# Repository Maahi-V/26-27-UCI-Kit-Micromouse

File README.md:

# UCI Kit Mouse (2026-2027 Ver.)

This repository contains:
 - A template kit mouse project with KiCad
 - Short installation guide for the overall project
 - Helpful Git Commands

> [!IMPORTANT]
> Contents here are summarized from [IEEE@UCI Micromouse Website](https://ieee.ics.uci.edu/micromouse/mm_index.html).
> More details of the tools installed will be under "Modules" and "Lectures."

## Prerequistes

### KiCad
> [!NOTE]
> All teamates should install the same version of KiCad, preferably the newest
> stable release here: https://www.kicad.org/download/. 
> Files modified from newer versions can no longer be read by older versions.

*The installation guide will be using KiCad ver. 10.5*

<details>
<summary><b>Windows</b></summary>

1. Download and Launch the installer: https://www.kicad.org/download/windows/

2. Select **Next** 2 times, and give permissions to the installer.

3. At "Choose Components," make sure all check boxes are selected 
(should be default)

4. Select **Next**, and then install.
</details>

<details>
<summary><b>macOS</b></summary>

1. Download the installer: https://www.kicad.org/download/macos/

2. Double-click `kicad-unified-universal-#.#.#.dmg` file in finder

3. Click and drag the `KiCad.app` to Application folder.

4. Close the window, and Eject the `.dmg` file from Finder.

</details>

<details>
<summary><b>Linux</b></summary>
Install as an AppImage or use your desired package manager. <br></br>

> [!NOTE]
> KiCad does not support Wayland,
> but the AppImage version defaults to Wayland instead of 
> Xwayland under GTK3. Installing via PPAs instead defaults to Xwayland, 
> likely bringing graphical bugs.

</details>

---
### Git
Check if Git is installed with this command:
```sh
git --version
```

If git is missing, here are official steps in 
[installing Git](https://git-scm.com/install/), and
a recommended step-by-step installation will be provided below.

<details>
<summary><b>Windows</b></summary>

1. Install **Git for Windows** from this link: [https://git-scm.com/install/windows](https://git-scm.com/install/windows).

2. After installing the executable, give the installer permissions.

3. Select **Next** 4 times, and reach "Choosing the default editor used by Git"

Choose your favorite editor, and after setup you can still change the 
default editor with this command:
```sh
git config --global core.editor "editor-name"
```

4. Select **Next** to "Adjusting the name of the initial branch in 
new repositories"
- Use default branch name as `main`, since GitHub defaults to `main` as well.

5. Keep selecting **Next** and finish installing.

</details>

<details>
<summary><b>macOS</b></summary>

Install **Xcode Command Line Tools** from Apple for `git` and other tools:
```sh
xcode-select --install
```
... and more info about what is downloaded is [here](https://developer.apple.com/documentation/xcode/installing-the-command-line-tools/).

If you prefer installing ONLY `git` with `homebrew`, here is the command:
```sh
brew install git
```
</details>

<details>
<summary><b>Linux</b></summary>

Install `git` with package manager or build from source, 
as seen from this site: [https://git-scm.com/install/linux](https://git-scm.com/install/linux).
</details>

---

#### Setting up GitHub Authentication

Source: [https://docs.github.com/en/authentication/keeping-your-account-and-data-secure/about-authentication-to-github](https://docs.github.com/en/authentication/keeping-your-account-and-data-secure/about-authentication-to-github)

After installing git, you need to configure a few things before being
able to edit your remote repositories on GitHub.

> [!NOTE]
> If Authentication is via GitHub Desktop, Git environment (in cli) does
> not also get authentication.
<details>
<summary><b>GitHub Desktop</b></summary>
Source: 

[https://docs.github.com/en/desktop/installing-and-authenticating-to-github-desktop/authenticating-to-github-in-github-desktop](https://docs.github.com/en/desktop/installing-and-authenticating-to-github-desktop/authenticating-to-github-in-github-desktop)

1. Install and Run GitHub Desktop: https://desktop.github.com/download/

2. Login or Create your GitHub account, and authorize access:

3. Setup your Git Username and Email
   - Select "Configure Manually" if `user.email` 
     and `user.name` have been setup before

</details>

<details>
<summary><b>GitHub CLI</b></summary>

Source: 
 - https://cli.github.com/manual/gh_auth_login
 - https://docs.github.com/en/github-cli/github-cli/quickstart#prerequisites
<br></br>
1. Install GitHub CLI with this link: https://cli.github.com/
2. Follow the prompts below:
   - Authentication with HTTPS, so authentication automatically
       used for HTTPS repo clones
   - `.gitconfig` will be modified

</details>

<details>
<summary><b>Personal Access Tokens</b></summary>

Source: https://docs.github.com/en/authentication/keeping-your-account-and-data-secure/managing-your-personal-access-tokens
</details>

---

#### Other Git Tools
For a GUI experience, try out these software:
 - Connecting GitHub to VS Code, and utilizing [Source Control](https://code.visualstudio.com/docs/sourcecontrol/overview)

## Cloning This Repository

<details>
<summary><b>GitHub Desktop</b></summary>

Source: [https://docs.github.com/en/desktop/adding-and-cloning-repositories/cloning-a-repository-from-github-to-github-desktop](https://docs.github.com/en/desktop/adding-and-cloning-repositories/cloning-a-repository-from-github-to-github-desktop).

1. At the top of this page, click the green button labled **<> Code**

2. Then select **Open with GitHub Desktop**

3. Choose where the local Clone Repo location, and then press **Clone**

</details>

<details>
<summary><b>On Terminal</b></summary>

Source: [https://docs.github.com/en/repositories/creating-and-managing-repositories/cloning-a-repository](https://docs.github.com/en/repositories/creating-and-managing-repositories/cloning-a-repository).

1. At the top of this page, click the green button labled **<> Code**

2. Copy the clone link as HTTPS

3. Open your terminal, change directory to somewhere you want to put your 
local repository in.

4. Type `git clone`, then paste and run the command:
```sh
$ git clone https://github.com/Maahi-V/26-27-UCI-Kit-Micromouse.git
>   Cloning into '26-27-UCI-Kit-Micromouse'...
>   remote: Enumerating objects: 135, done.
>   remote: Counting objects: 100% (135/135), done.
>   remote: Compressing objects: 100% (78/78), done.
>   remote: Total 135 (delta 69), reused 118 (delta 52), pack-reused 0 (from 0)
>   Receiving objects: 100% (135/135), 3.28 MiB | 12.25 MiB/s, done.
>   Resolving deltas: 100% (69/69), done.
```
</details>

## Push Local Repository into a GitHub Remote Repository (Initial)

<details>
<summary><b>GitHub Desktop</b></summary>

1. Find you local git repository in your file manager, and make sure you 
   have hidden files enabled
   - Windows: In File Explorer, go to View -> Show -> Hidden Items
   - macOS: In finder, use `Cmd + Shift + .` to show hidden files

2. Delete the `.git` folder (contains the local repo edit history) and 
   revert the local repository back to a normal folder
   - After cloning the repository, it still has commits made by other 
     people. To start fresh, these commits needs to be deleted

3. GitHub Desktop should now have an error popup, and **"Remove"** this repo
   to stop tracking it

4. Select **Add an Existing Repository from your Local Drive...**

5. Find the location of the local repo (default location is `~/Documents/GitHub/`), and
   press **Add Repository**

6. Now select **create a repository**

7. GitHub Desktop automatically fills out everything required. Keep
   everything as default and select **Create Repository**

8. After creation, GitHub Desktop would automatically create a commit.
   Select the **Publish repository** to create a new remote repo

9. Insert a name and description of the project, and select **Publish Repository**

10. Now you can view your repository on browser as well

</details>

<details>
<summary><b>With `github.com` and Terminal</b></summary>

1. Go to your GitHub Dashboard (at [https://github.com/](https://github.com/) and login),
and press the **+** button, then **New repository**

2. Configure your repository to whatever you like, just make sure
   these 2 settings are set (since cloned repo already has a README
   and `.gitignore` configured)

3. Now you should see **Quick Setup**, but the local repository
   needs to be modified a bit before being pushed to the remote
   server.

4. Go back to your local git repository, and make sure you have
   hidden files enabled
   - Windows: In File Explorer, go to View -> Show -> Hidden Items
   - macOS: In finder, use `Cmd + Shift + .` to show hidden files

5. Delete the `.git` folder (contains the local repo edit history) and 
   revert the local repository back to a normal folder
   - After cloning the repository, it still has commits made by other 
     people. To start fresh, these commits needs to be deleted

6. Copy-paste this command to create a new local git repository: 
```
git init
git add -A
git commit -m "First Commit"
```

7. Then go back to GitHub, and copy-paste the commands under 
 **…or push an existing repository from the command line**

8. Reload the GitHub page, and your remote repository should now
   show up

</details>

> [!TIP]
> Update and personalize this README page! Feel free to edit/replace 
> the README.md to be about your project instead.

## Push Local Edits to Remote Repository

When sharing edits to other teamates, users have to use `git push` 
push/share their local edits to the remote repository. 

Teamates then need to use `git pull` to obtain 
the new edits to their local repository.

The example below has the following local edits:
 - `README.md` file modified
 - New file `temp.txt`

When pushing edits to the remote server, *you can control what remote file
gets updated* by staging the local files you want to be updated.

In this example ONLY the `README.md` edits are shared, 
and `temp.txt` is not shared.

<details>
<summary><b>GitHub Desktop</b></summary>
1. GitHub Desktop should have an overview of the local edits made.

Here is `README.md`

... and here is `temp.txt`

2. Only the `README.md` file should get updated, so unstage `temp.txt` 
   by unchecking this box at the left

The bottom **Commit 2 files to main** button should now change to **Commit 1 file to main** instead

3. Write a Commit Message and Description, and press **Commit 1 file to main** 
   to create a new commit
   - Commits are saved as an edit history
   - Use commits as a checkpoint completed, and to organize the work you made
   - This commit is only recorded locally
   - Commit Summary: Write a concise change made, and easy to understand
   - If needed, add more details in Commit Description

Edits from `temp.txt` has not been recorded/commit, so GitHub Desktop
still display the file

4. Now push your local commits to origin (the remote server)
 - Recommended to push multiple commits at once, instead of commit once then immediately push.
 - It is easier to fix mistakes in local commits that are not pushed yet, 
   or to squash multiple local commits into one for a cleaner commit history

</details>

<details>
<summary><b>On Terminal</b></summary>

1. Check overall status of the local repo with `git status`
 - Modified File: File already on remote server, but locally is edited
 - Untracked files: New file not tracked by remote server
```
$ git status
On branch main
Your branch is up to date with 'origin/main'.

Changes not staged for commit:
  (use "git add <file>..." to update what will be committed)
  (use "git restore <file>..." to discard changes in working directory)
	modified:   README.md

Untracked files:
  (use "git add <file>..." to include in what will be committed)
	temp.txt

no changes added to commit (use "git add" and/or "git commit -a")
```

2. Only stage `README.md` with `git add <file>`
 - Also you can stage all files with `git add -A`
```
$ git add README.md
$ git status
On branch main
Your branch is up to date with 'origin/main'.

Changes to be committed:
  (use "git restore --staged <file>..." to unstage)
	modified:   README.md

Untracked files:
  (use "git add <file>..." to include in what will be committed)
	temp.txt
```

3. Create a commit with `git commit`, and use `-m` to append the commit
   message
```
$ git commit -m "Modified README.md"
[main 7311eae] Modified README.md
 1 file changed, 1 insertion(+)
```

Now local repo should be ahead of `origin/main` (since local repo has newer commits than remote repo),
and `temp.txt` is not included in the commit
```
$ git status
On branch main
Your branch is ahead of 'origin/main' by 1 commit.
  (use "git push" to publish your local commits)

Untracked files:
  (use "git add <file>..." to include in what will be committed)
	temp.txt

nothing added to commit but untracked files present (use "git add" to track)

$ git whatchanged
commit 7311eae2b4a877c8229590e44fe4e0f08f418967 (HEAD -> main)
Author: Justin Chen <justin7.chen@gmail.com>
Date:   Mon Sep 28 00:05:22 2026 -0700

    Modified README.md

:100644 100644 404fe81 91129e9 M        README.md
```

4. Now push your local edits to remote server with `git push`
```
$ git push
Enumerating objects: 5, done.
Counting objects: 100% (5/5), done.
Delta compression using up to 12 threads
Compressing objects: 100% (2/2), done.
Writing objects: 100% (3/3), 279 bytes | 279.00 KiB/s, done.
Total 3 (delta 1), reused 0 (delta 0), pack-reused 0 (from 0)
remote: Resolving deltas: 100% (1/1), completed with 1 local object.
To https://github.com/hippoBus/testin.git
   0ab9dcf..7311eae  main -> main
```

</details>

## Pull Remote Edits to Local Repository

<details>
<summary><b>GitHub Desktop</b></summary>

1. If available, select **Fetch Origin** to check if there are any new
   remote edits

2. Detected that the remote repository is updated, button becomes **Pull Origin**

3. Now the local repository is updated. Check **History** to see what
   edits are made

</details>

<details>
<summary><b>On Terminal</b></summary>

1. Check if there are any remote changes with `git fetch`
  - No changes, `git fetch` results without any output
```
$ git fetch
remote: Enumerating objects: 5, done.
remote: Counting objects: 100% (5/5), done.
remote: Compressing objects: 100% (2/2), done.
remote: Total 3 (delta 1), reused 0 (delta 0), pack-reused 0 (from 0)
Unpacking objects: 100% (3/3), 908 bytes | 151.00 KiB/s, done.
From https://github.com/hippoBus/testin
   7311eae..97050af  main       -> origin/main
```

2. Obtain new changes and rebase to edits in `origin/main` with `git pull`
```
$ git pull
Updating 7311eae..97050af
Fast-forward
 README.md | 3 +--
 1 file changed, 1 insertion(+), 2 deletions(-)
```

</details>

## Helpful Git Commands

For more details, use the `man git` command or use the official
documentation: [https://git-scm.com/docs](https://git-scm.com/docs).

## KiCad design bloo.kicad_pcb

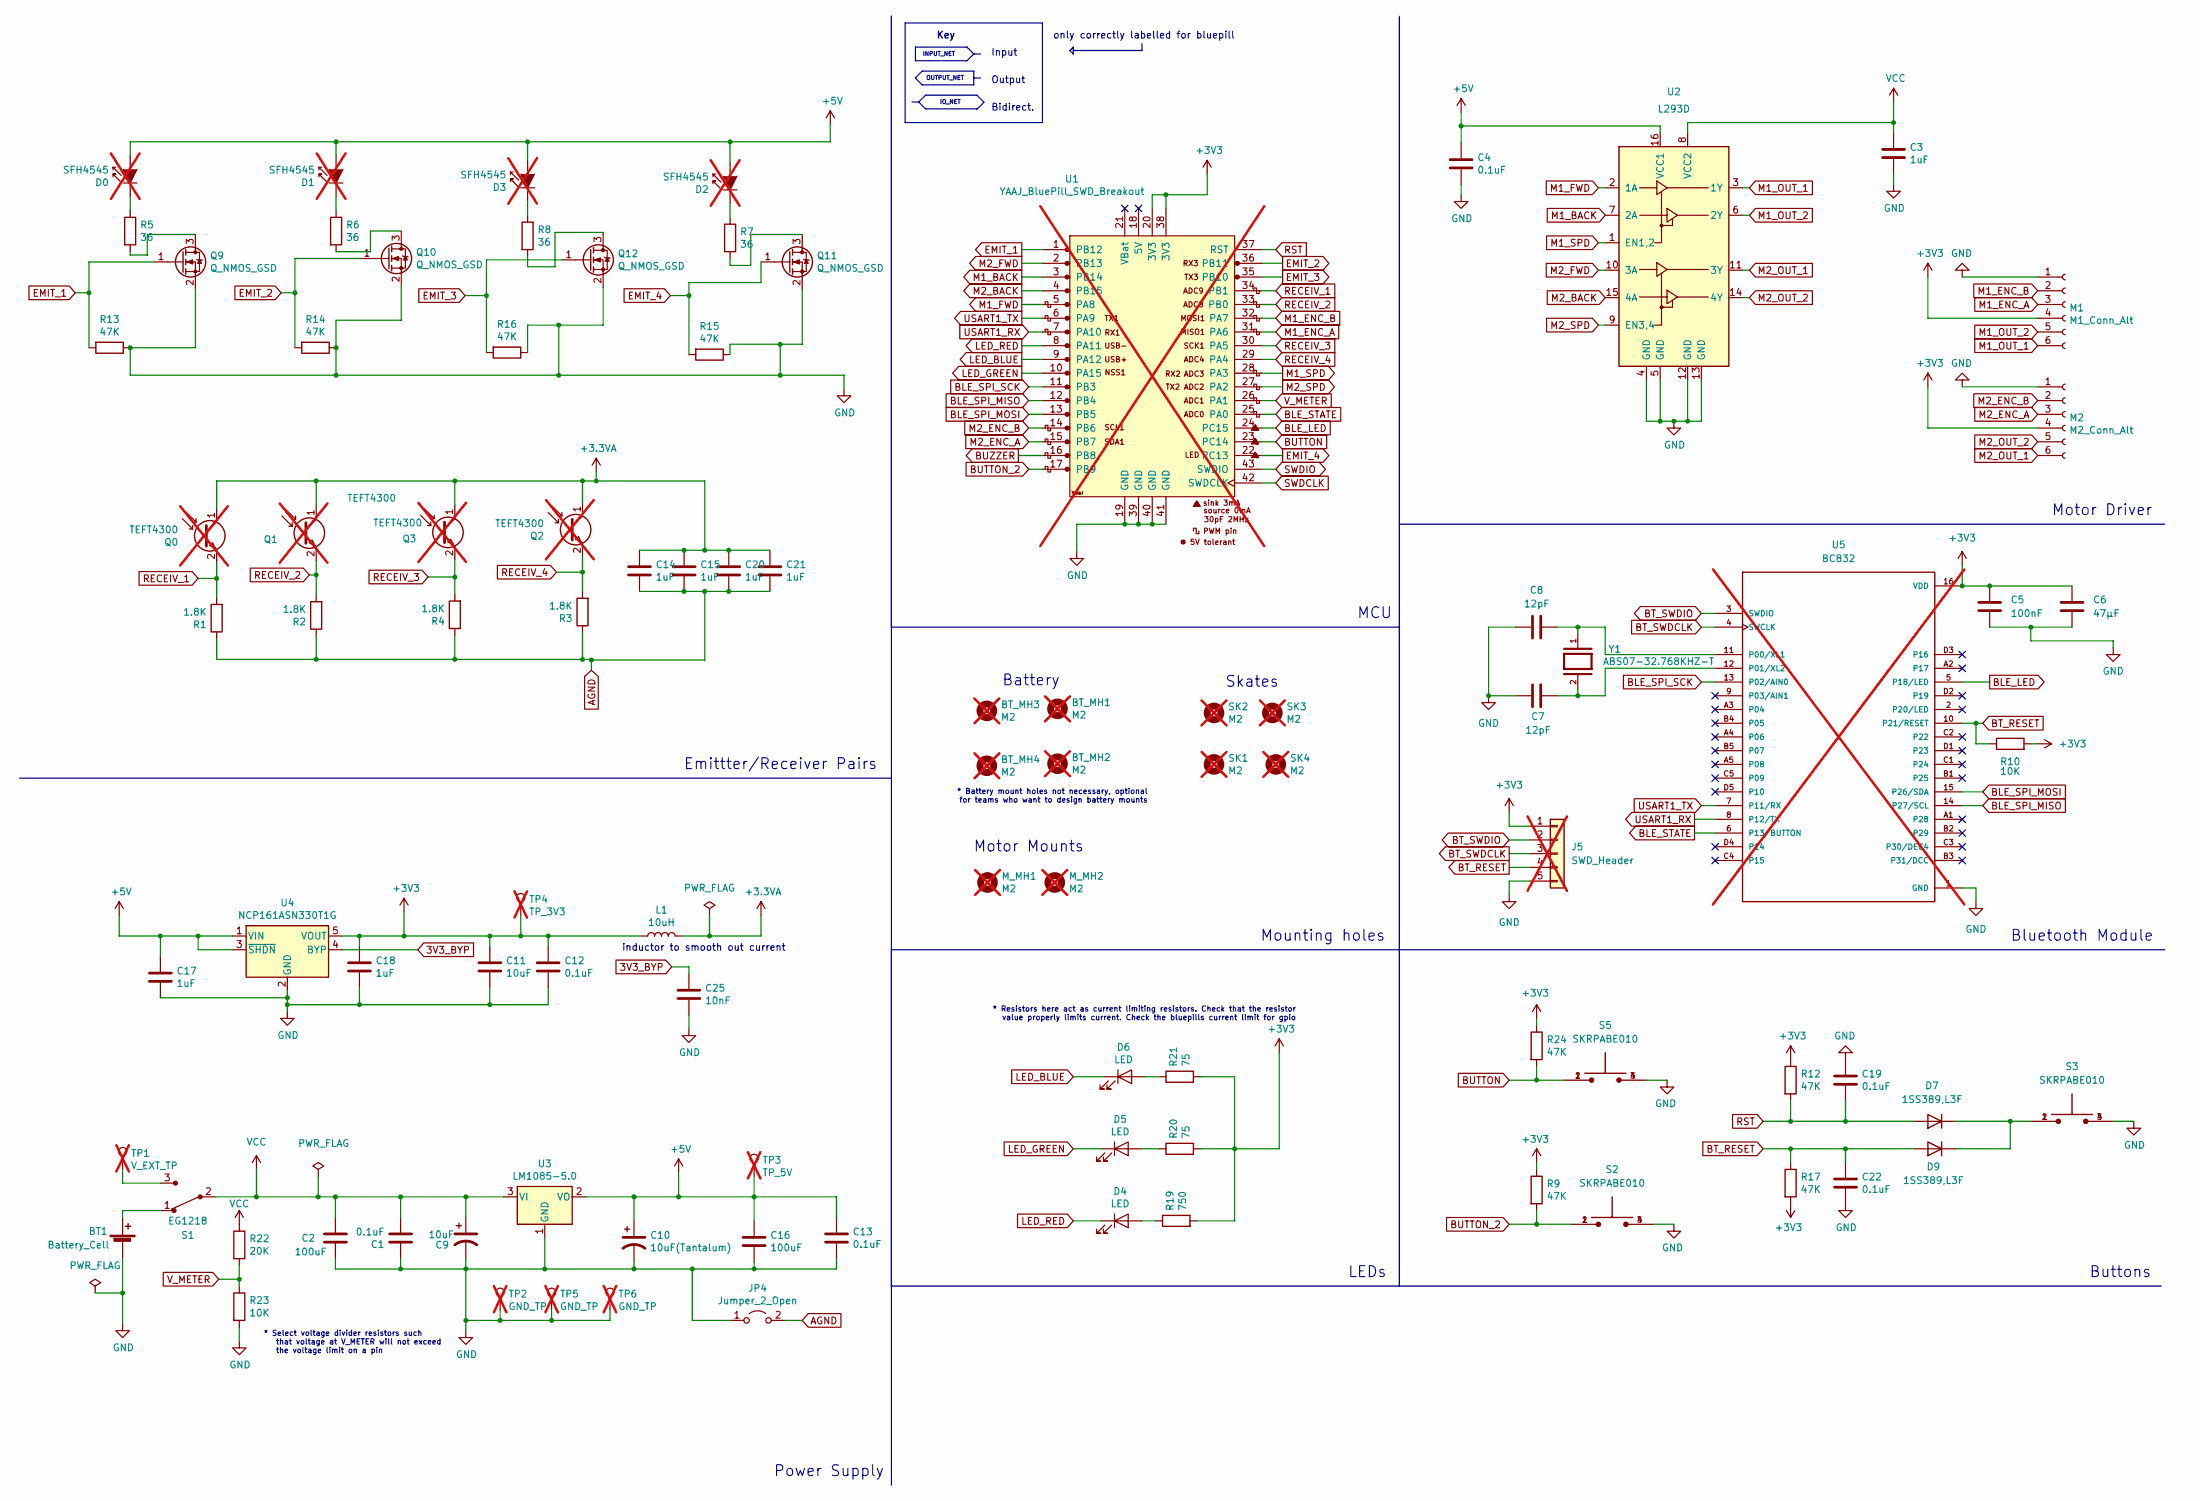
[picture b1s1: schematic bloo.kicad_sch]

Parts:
BT1: Battery_Cell; AMASS_XT30UPB-M_1x02_P5.0mm_Vertical; LCSC Part # C99101
BT_MH1, BT_MH2, BT_MH3, BT_MH4: M2; MountingHole_2.2mm_M2; not fitted
C1, C4, C12, C13, C19, C22: 0.1uF; C_1206_3216Metric_Pad1.33x1.80mm_HandSolder; LCSC Part # C1945
C2, C16: 100uF; CP_Radial_D6.3mm_P2.50mm; LCSC Part # C1590882
C3, C14, C15, C17, C18, C20, C21: 1uF; C_1206_3216Metric_Pad1.33x1.80mm_HandSolder; LCSC Part # C28322
C5: 100nF; C_0603_1608Metric; LCSC Part # C1590
C6: 47µF; C_1206_3216Metric; LCSC Part # C68361
C7, C8: 12pF; C_0603_1608Metric_Pad1.08x0.95mm_HandSolder; LCSC Part # C38523
C9, C11: 10uF; C_1206_3216Metric_Pad1.33x1.80mm_HandSolder; LCSC Part # C39127
C10: 10uF(Tantalum); C_1206_3216Metric_Pad1.33x1.80mm_HandSolder; LCSC Part # C1952791
C25: 10nF; C_1206_3216Metric_Pad1.33x1.80mm_HandSolder; LCSC Part # C1846
D0, D1, D2, D3: SFH4545; Emitter; LCSC Part # C2900370; not fitted
D4: LED; LED_0805_2012Metric_Pad1.15x1.40mm_HandSolder; LCSC Part # C5879380
D5: LED; LED_0805_2012Metric_Pad1.15x1.40mm_HandSolder; LCSC Part # C2890404
D6: LED; LED_0805_2012Metric_Pad1.15x1.40mm_HandSolder; LCSC Part # C2293
D7, D9: 1SS389,L3F; D_SOD-523; LCSC Part # C516855
J5: SWD_Header; PinHeader_1x05_P2.54mm_Vertical; not fitted
JP4: Jumper_2_Open; SolderJumper-2_P1.3mm_Bridged_Pad1.0x1.5mm
L1: 10uH; L_1206_3216Metric_Pad1.42x1.75mm_HandSolder; LCSC Part # C845121
M1: M1_Conn_Alt; JST_SH_BM06B-SRSS-TB_1x06-1MP_P1.00mm_Vertical; LCSC Part # C144397
M2: M2_Conn_Alt; JST_SH_BM06B-SRSS-TB_1x06-1MP_P1.00mm_Vertical; LCSC Part # C144397
M_MH1, M_MH2: M2; Motor_mouse; not fitted
Q0, Q1, Q2, Q3: TEFT4300; Emitter; LCSC Part # C118301; not fitted
Q9, Q10, Q11, Q12: Q_NMOS_GSD; SOT-23; LCSC Part # C5310967
R1, R2, R3, R4: 1.8K; R_1206_3216Metric_Pad1.30x1.75mm_HandSolder; LCSC Part # C22108
R5, R6, R7, R8: 36; R_1206_3216Metric_Pad1.30x1.75mm_HandSolder; LCSC Part # C18006
R9, R12, R13, R14, R15, R16, R17, R24: 47K; R_1206_3216Metric_Pad1.30x1.75mm_HandSolder; LCSC Part # C25664
R10, R23: 10K; R_1206_3216Metric_Pad1.30x1.75mm_HandSolder; LCSC Part # C2479071
R19: 750; R_1206_3216Metric_Pad1.30x1.75mm_HandSolder; LCSC Part # C17985
R20, R21: 75; R_1206_3216Metric_Pad1.30x1.75mm_HandSolder; LCSC Part # C17987
R22: 20K; R_1206_3216Metric_Pad1.30x1.75mm_HandSolder; LCSC Part # C18003
S1: EG1218; MM Switch; MPN EG1218; Digi-Key_PN EG1903-ND
S2, S3, S5: SKRPABE010; SW4_SKRPABE010_ALPS; LCSC Part # C778166
SK1, SK2, SK3, SK4: M2; MountingHole_2.2mm_M2; not fitted
TP1: V_EXT_TP; PinHeader_1x01_P2.54mm_Vertical; not fitted
TP2, TP5, TP6: GND_TP; PinHeader_1x01_P2.54mm_Vertical; not fitted
TP3: TP_5V; PinHeader_1x01_P2.54mm_Vertical; not fitted
TP4: TP_3V3; PinHeader_1x01_P2.54mm_Vertical; not fitted
U1: YAAJ_BluePill_SWD_Breakout; STM32F103; not fitted
U2: L293D; DIP-16_W7.62mm; LCSC Part # C12340
U3: LM1085-5.0; 5V Voltage Reg; LCSC Part # C129950
U4: NCP161ASN330T1G; SOT-23-5; LCSC Part # C892187
U5: BC832; XCVR_BC832; PARTREV 2.02; not fitted
Y1: ABS07-32.768KHZ-T; CAP_ABS07-32.768KHZ-T_ABR; PARTREV 08.19.15; LCSC Part # C130253

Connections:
3V3_BYP: C25.1, U4.4 (BYP)
+3.3VA: C14.1, C15.1, C20.1, C21.1, L1.2, Q0.1 (C), Q1.1 (C), Q2.1 (C), Q3.1 (C)
+3V3: C5.1, C6.1, C11.1, C12.1, C18.1, J5.1, L1.1, M1.4, M2.4, R9.1, R10.2, R12.1, R17.2, R19.2, R20.2, R21.2, R24.1, TP4.1, U1.20 (3V3), U1.38 (3V3), U4.5 (VOUT), U5.16 (VDD)
+5V: C4.1, C10.1, C13.1, C16.1, C17.1, D0.2 (A), D1.2 (A), D2.2 (A), D3.2 (A), TP3.1, U2.16 (VCC1), U3.2 (VO), U4.1 (VIN), U4.3 (~SHDN)
AGND: C14.2, C15.2, C20.2, C21.2, JP4.2 (B), R1.1, R2.1, R3.1, R4.1
BLE_LED: U1.24 (PC15), U5.5 (P18/LED)
BLE_SPI_MISO: U1.12 (PB4), U5.14 (P27/SCL)
BLE_SPI_MOSI: U1.13 (PB5), U5.15 (P26/SDA)
BLE_SPI_SCK: U1.11 (PB3), U5.13 (P02/AIN0)
BLE_STATE: U1.25 (PA0), U5.6 (P13/BUTTON)
BT_RESET: C22.1, D9.2 (A), J5.4, R10.1, R17.1, U5.10 (P21/RESET)
BT_SWDCLK: J5.3, U5.4 (SWCLK)
BT_SWDIO: J5.2, U5.3 (SWDIO)
BUTTON: R24.2, S5.1, S5.2, U1.23 (PC14)
BUTTON_2: R9.2, S2.1, S2.2, U1.17 (PB9)
BUZZER: U1.16 (PB8)
EMIT_1: Q9.1 (G), R13.2, U1.1 (PB12)
EMIT_2: Q10.1 (G), R14.2, U1.36 (PB11)
EMIT_3: Q12.1 (G), R16.2, U1.35 (PB10)
EMIT_4: Q11.1 (G), R15.2, U1.22 (PC13)
GND: BT1.2 (-), C1.1, C2.2, C3.2, C4.2, C5.2, C6.2, C7.1, C8.1, C9.2, C10.2, C11.2, C12.2, C13.2, C16.2, C17.2, C18.2, C19.1, C22.2, C25.2, J5.5, JP4.1 (A), M1.1, M2.1, Q9.2 (S), Q10.2 (S), Q11.2 (S), Q12.2 (S), R13.1, R14.1, R15.1, R16.1, R23.2, S2.3, S2.4, S3.3, S3.4, S5.3, S5.4, TP2.1, TP5.1, TP6.1, U1.19 (GND), U1.39 (GND), U1.40 (GND), U1.41 (GND), U2.4 (GND), U2.5 (GND), U2.12 (GND), U2.13 (GND), U3.1 (GND), U4.2 (GND), U5.1 (GND)
LED_BLUE: D6.1 (K), U1.9 (PA12)
LED_GREEN: D5.1 (K), U1.10 (PA15)
LED_RED: D4.1 (K), U1.8 (PA11)
M1_BACK: U1.3 (PB14), U2.7 (2A)
M1_ENC_A: M1.3, U1.31 (PA6)
M1_ENC_B: M1.2, U1.32 (PA7)
M1_FWD: U1.5 (PA8), U2.2 (1A)
M1_OUT_1: M1.6, U2.3 (1Y)
M1_OUT_2: M1.5, U2.6 (2Y)
M1_SPD: U1.28 (PA3), U2.1 (EN1,2)
M2_BACK: U1.4 (PB15), U2.15 (4A)
M2_ENC_A: M2.3, U1.15 (PB7)
M2_ENC_B: M2.2, U1.14 (PB6)
M2_FWD: U1.2 (PB13), U2.10 (3A)
M2_OUT_1: M2.6, U2.11 (3Y)
M2_OUT_2: M2.5, U2.14 (4Y)
M2_SPD: U1.27 (PA2), U2.9 (EN3,4)
unnamed: BT1.1 (+), S1.1
unnamed: D0.1 (K), R5.1
unnamed: D1.1 (K), R6.1
unnamed: D2.1 (K), R7.1
unnamed: D3.1 (K), R8.1
unnamed: D4.2 (A), R19.1
unnamed: D5.2 (A), R20.1
unnamed: D6.2 (A), R21.1
unnamed: D7.1 (K), D9.1 (K), S3.1, S3.2
unnamed: Q9.3 (D), R5.2
unnamed: Q10.3 (D), R6.2
unnamed: Q11.3 (D), R7.2
unnamed: Q12.3 (D), R8.2
unnamed: S1.3, TP1.1
unnamed: C8.2, U5.11 (P00/XL1), Y1.1
unnamed: C7.2, U5.12 (P01/XL2), Y1.2
RECEIV_1: Q0.2 (E), R1.2, U1.34 (PB1)
RECEIV_2: Q1.2 (E), R2.2, U1.33 (PB0)
RECEIV_3: Q3.2 (E), R4.2, U1.30 (PA5)
RECEIV_4: Q2.2 (E), R3.2, U1.29 (PA4)
RST: C19.2, D7.2 (A), R12.2, U1.37 (RST)
USART1_RX: U1.7 (PA10), U5.8 (P12/TX)
USART1_TX: U1.6 (PA9), U5.7 (P11/RX)
VCC: C1.2, C2.1, C3.1, C9.1, R22.1, S1.2, U2.8 (VCC2), U3.3 (VI)
V_METER: R22.2, R23.1, U1.26 (PA1)

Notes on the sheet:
Mounting holes
Bluetooth Module
Output
IO_NET
Battery
Input
inductor to smooth out current
* Battery mount holes not necessary, optional for teams who want to design battery mounts
Motor Driver
Emittter/Receiver Pairs
* Resistors here act as current limiting resistors. Check that the resistor value properly limits current. Check the bluepills current limit for gpio
LEDs
Bidirect.
MCU
OUTPUT_NET
only correctly labelled for bluepill
* Select voltage divider resistors such that voltage at V_METER will not exceed the voltage limit on a pin
Motor Mounts
Buttons
Skates
Power Supply
Key
INPUT_NET

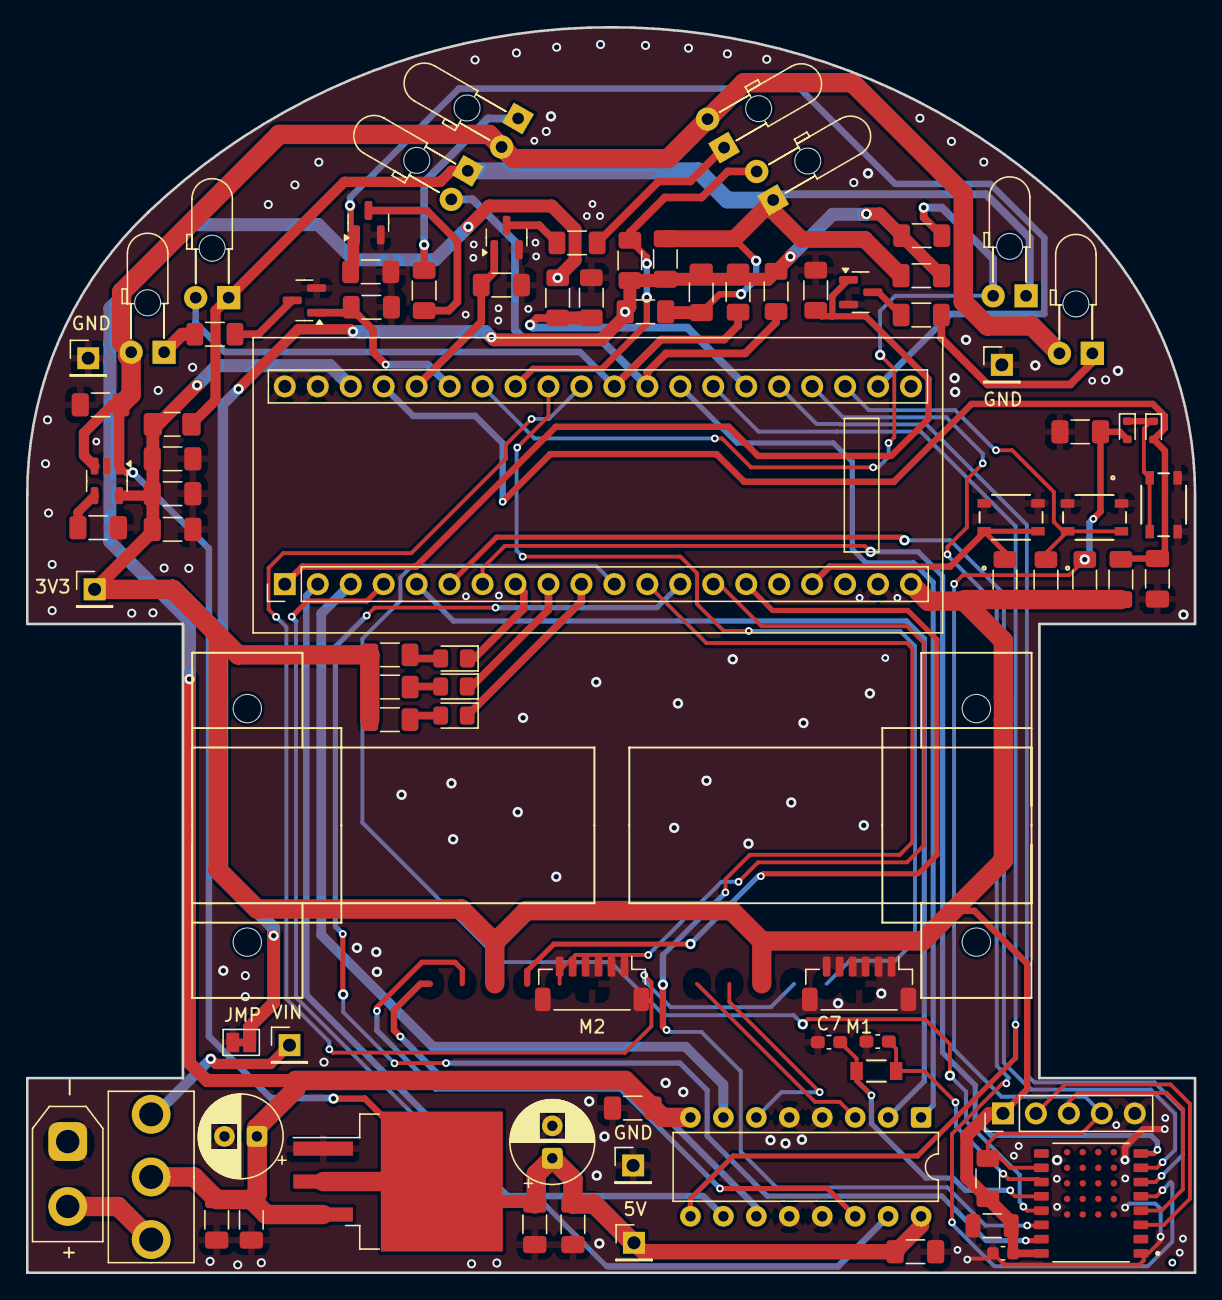
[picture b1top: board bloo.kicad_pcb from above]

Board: 2 copper layers, 90.0 x 96.0 mm, 94 parts (0 on the bottom side), 62 nets.

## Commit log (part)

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2026-06-16 25-26 bare mouse original kit mouse schematic
2026-06-17 Removed o-ring, SWD Header, and Buzzer circuit
2026-06-30 Removed green breakout board with generic 6 pin JST connector (3A)
2026-06-30 linked datasheet for new JST encoder connector part M1/M2
